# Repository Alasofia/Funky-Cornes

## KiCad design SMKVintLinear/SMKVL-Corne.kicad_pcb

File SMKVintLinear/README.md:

# MXMLP-Corne
Corne made with my MXMountLP footprints

If you intend to sell this for profit, please contact me by email or on Discord.
alas@duck.com / Alas#5007

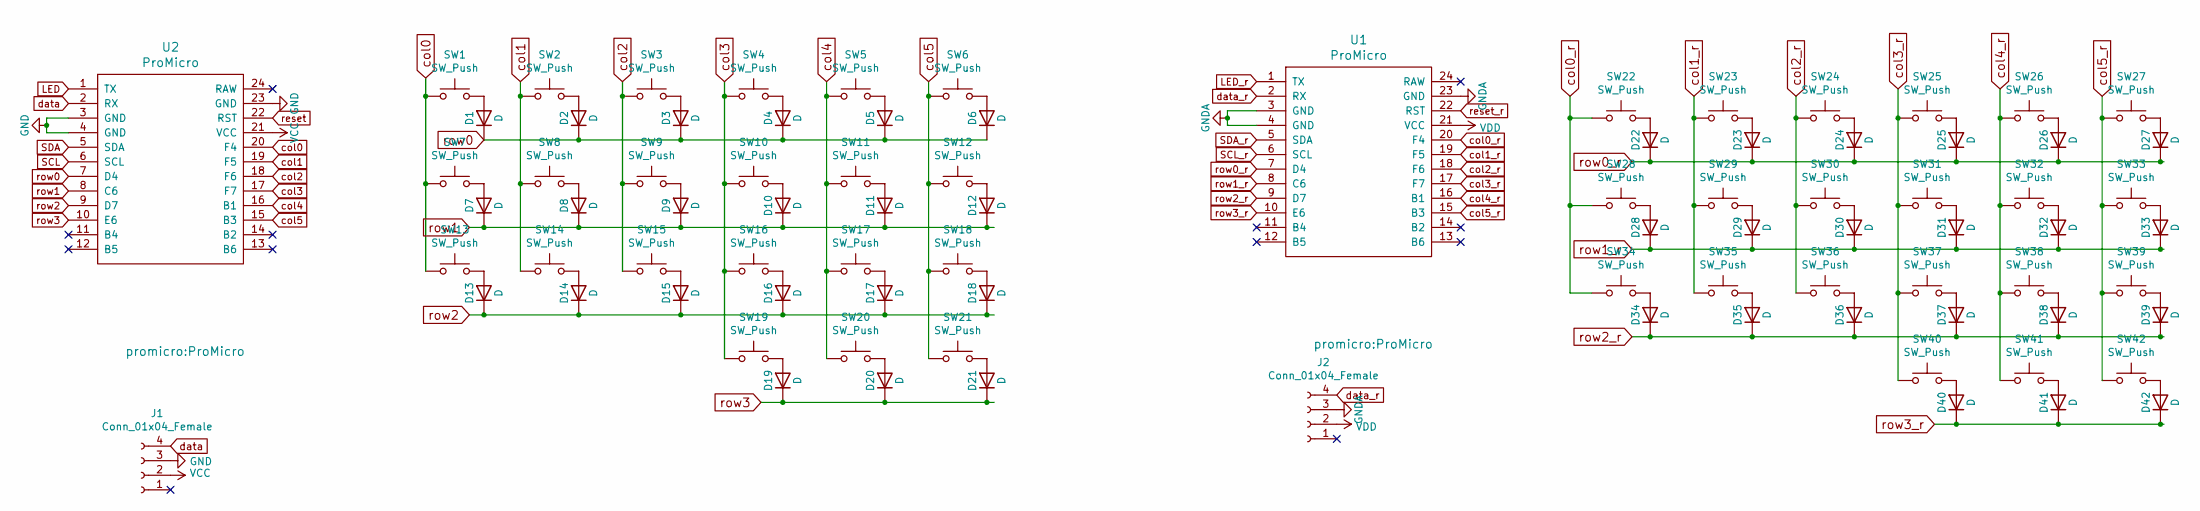
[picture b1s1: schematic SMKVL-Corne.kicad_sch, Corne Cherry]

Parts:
D1, D2, D3, D4, D5, D6, D7, D8, D9, D10, D11, D12, D13, D14, D15, D16, D17, D18, D19, D20, D21, D22, D23, D24, D25, D26, D27, D28, D29, D30, D31, D32, D33, D34, D35, D36, D37, D38, D39, D40, D41, D42: D; Diode-Hybrid-Back
J1, J2: Conn_01x04_Female; TRRS-PJ-320A
SW1, SW2, SW3, SW4, SW5, SW6, SW7, SW8, SW9, SW10, SW11, SW12, SW13, SW14, SW15, SW16, SW17, SW18, SW19, SW20, SW21, SW22, SW23, SW24, SW25, SW26, SW27, SW28, SW29, SW30, SW31, SW32, SW33, SW34, SW35, SW36, SW37, SW38, SW39, SW40, SW41, SW42: SW_Push; SMK-JM0404-1U
U1, U2: ProMicro

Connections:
GND: J1.3, U2.3 (GND), U2.4 (GND), U2.23 (GND)
GNDA: J2.3, U1.3 (GND), U1.4 (GND), U1.23 (GND)
LED: U2.1 (TX)
LED_r: U1.1 (TX)
unnamed: D1.2 (A), SW1.2
unnamed: D2.2 (A), SW2.2
unnamed: D3.2 (A), SW3.2
unnamed: D4.2 (A), SW4.2
unnamed: D5.2 (A), SW5.2
unnamed: D6.2 (A), SW6.2
unnamed: D7.2 (A), SW7.2
unnamed: D8.2 (A), SW8.2
unnamed: D9.2 (A), SW9.2
unnamed: D10.2 (A), SW10.2
unnamed: D11.2 (A), SW11.2
unnamed: D12.2 (A), SW12.2
unnamed: D13.2 (A), SW13.2
unnamed: D14.2 (A), SW14.2
unnamed: D15.2 (A), SW15.2
unnamed: D16.2 (A), SW16.2
unnamed: D17.2 (A), SW17.2
unnamed: D18.2 (A), SW18.2
unnamed: D19.2 (A), SW19.2
unnamed: D20.2 (A), SW20.2
unnamed: D21.2 (A), SW21.2
unnamed: D22.2 (A), SW22.2
unnamed: D23.2 (A), SW23.2
unnamed: D24.2 (A), SW24.2
unnamed: D25.2 (A), SW25.2
unnamed: D26.2 (A), SW26.2
unnamed: D27.2 (A), SW27.2
unnamed: D28.2 (A), SW28.2
unnamed: D29.2 (A), SW29.2
unnamed: D30.2 (A), SW30.2
unnamed: D31.2 (A), SW31.2
unnamed: D32.2 (A), SW32.2
unnamed: D33.2 (A), SW33.2
unnamed: D34.2 (A), SW34.2
unnamed: D35.2 (A), SW35.2
unnamed: D36.2 (A), SW36.2
unnamed: D37.2 (A), SW37.2
unnamed: D38.2 (A), SW38.2
unnamed: D39.2 (A), SW39.2
unnamed: D40.2 (A), SW40.2
unnamed: D41.2 (A), SW41.2
unnamed: D42.2 (A), SW42.2
SCL: U2.6 (SCL)
SCL_r: U1.6 (SCL)
SDA: U2.5 (SDA)
SDA_r: U1.5 (SDA)
VCC: J1.2, U2.21 (VCC)
VDD: J2.2, U1.21 (VCC)
col0: SW1.1, SW7.1, SW13.1, U2.20 (F4)
col0_r: SW22.1, SW28.1, SW34.1, U1.20 (F4)
col1: SW2.1, SW8.1, SW14.1, U2.19 (F5)
col1_r: SW23.1, SW29.1, SW35.1, U1.19 (F5)
col2: SW3.1, SW9.1, SW15.1, U2.18 (F6)
col2_r: SW24.1, SW30.1, SW36.1, U1.18 (F6)
col3: SW4.1, SW10.1, SW16.1, SW19.1, U2.17 (F7)
col3_r: SW25.1, SW31.1, SW37.1, SW40.1, U1.17 (F7)
col4: SW5.1, SW11.1, SW17.1, SW20.1, U2.16 (B1)
col4_r: SW26.1, SW32.1, SW38.1, SW41.1, U1.16 (B1)
col5: SW6.1, SW12.1, SW18.1, SW21.1, U2.15 (B3)
col5_r: SW27.1, SW33.1, SW39.1, SW42.1, U1.15 (B3)
data: J1.4, U2.2 (RX)
data_r: J2.4, U1.2 (RX)
reset: U2.22 (RST)
reset_r: U1.22 (RST)
row0: D1.1 (K), D2.1 (K), D3.1 (K), D4.1 (K), D5.1 (K), D6.1 (K), U2.7 (D4)
row0_r: D22.1 (K), D23.1 (K), D24.1 (K), D25.1 (K), D26.1 (K), D27.1 (K), U1.7 (D4)
row1: D7.1 (K), D8.1 (K), D9.1 (K), D10.1 (K), D11.1 (K), D12.1 (K), U2.8 (C6)
row1_r: D28.1 (K), D29.1 (K), D30.1 (K), D31.1 (K), D32.1 (K), D33.1 (K), U1.8 (C6)
row2: D13.1 (K), D14.1 (K), D15.1 (K), D16.1 (K), D17.1 (K), D18.1 (K), U2.9 (D7)
row2_r: D34.1 (K), D35.1 (K), D36.1 (K), D37.1 (K), D38.1 (K), D39.1 (K), U1.9 (D7)
row3: D19.1 (K), D20.1 (K), D21.1 (K), U2.10 (E6)
row3_r: D40.1 (K), D41.1 (K), D42.1 (K), U1.10 (E6)

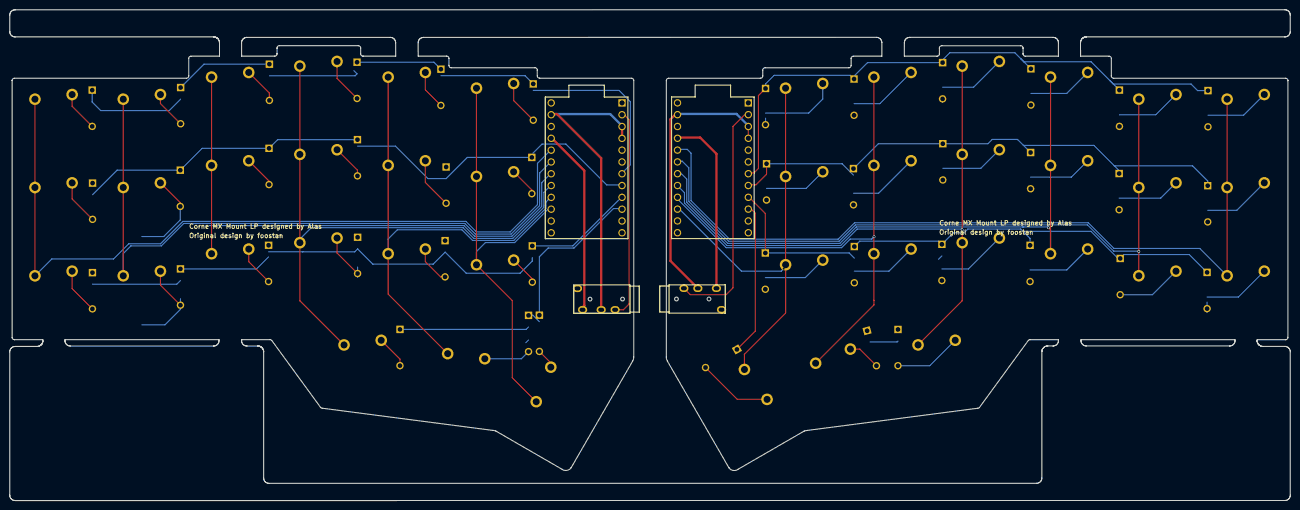
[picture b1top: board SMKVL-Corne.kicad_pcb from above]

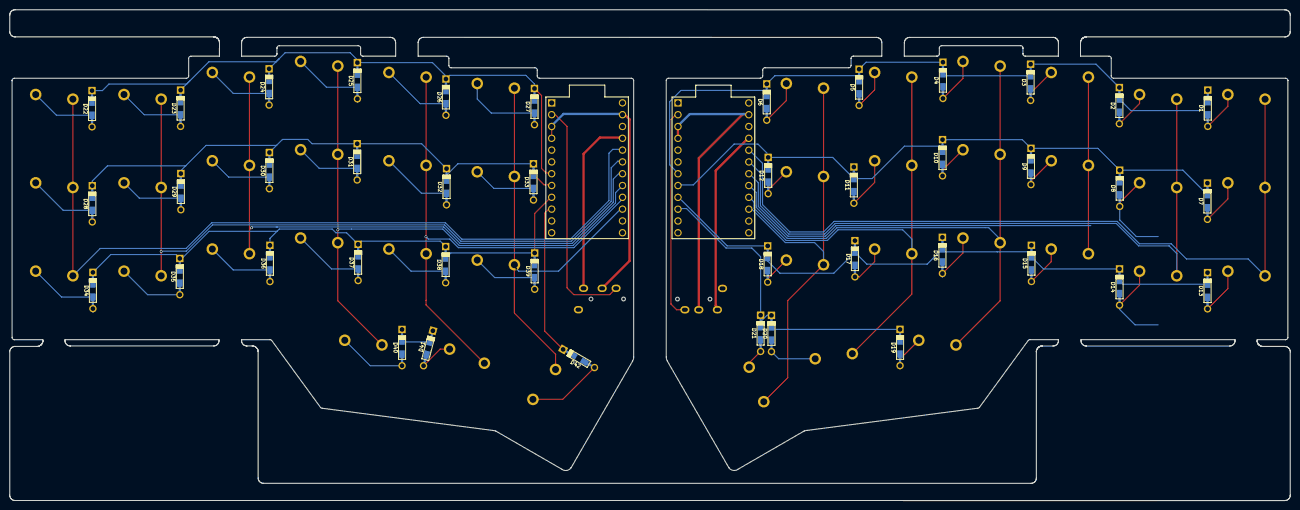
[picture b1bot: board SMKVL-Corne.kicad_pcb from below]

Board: 2 copper layers, 275.5 x 105.6 mm, 88 parts (2 on the bottom side), 68 nets.

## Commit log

2022-09-29 Consolidate MXMLP Corne into this repository. Started and Finished SMK Vintage Linear Corne.
